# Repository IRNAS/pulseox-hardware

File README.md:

# pulseox-hardware

---

#### License

All our projects are as usefully open-source as possible.

Hardware including documentation is licensed under [CERN OHL v.1.2. license](http://www.ohwr.org/licenses/cern-ohl/v1.2)

Firmware and software originating from the project is licensed under [GNU GENERAL PUBLIC LICENSE v3](http://www.gnu.org/licenses/gpl-3.0.en.html).

Open data generated by our projects is licensed under [CC0](https://creativecommons.org/publicdomain/zero/1.0/legalcode).

All our websites and additional documentation are licensed under [Creative Commons Attribution-ShareAlike 4 .0 Unported License] (https://creativecommons.org/licenses/by-sa/4.0/legalcode).

What this means is that you can use hardware, firmware, software and documentation without paying a royalty and knowing that you'll be able to use your version forever. You are also free to make changes but if you share these changes then you have to do so on the same conditions that you enjoy.

Koruza, GoodEnoughCNC and IRNAS are all names and marks of Institut IRNAS Rače. 
You may use these names and terms only to attribute the appropriate entity as required by the Open Licences referred to above. You may not use them in any other way and in particular you may not use them to imply endorsement or authorization of any hardware that you design, make or sell.

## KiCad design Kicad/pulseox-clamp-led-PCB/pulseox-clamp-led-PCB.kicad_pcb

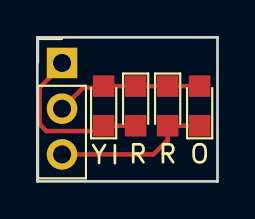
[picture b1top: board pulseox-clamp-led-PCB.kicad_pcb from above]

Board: 2 copper layers, 10.0 x 8.0 mm, 5 parts (0 on the bottom side), 3 nets.

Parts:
I: LED; LED_0805
O: LED; LED_0805
P1: Header 3; Pin_Header_Straight_1x03_Pitch2.54mm
R: LED; LED_0805
Y: LED; LED_0805

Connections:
unnamed: I.2, P1.1, Y.1
unnamed: I.1, O.2, P1.2, R.1, Y.2
unnamed: O.1, P1.3, R.2

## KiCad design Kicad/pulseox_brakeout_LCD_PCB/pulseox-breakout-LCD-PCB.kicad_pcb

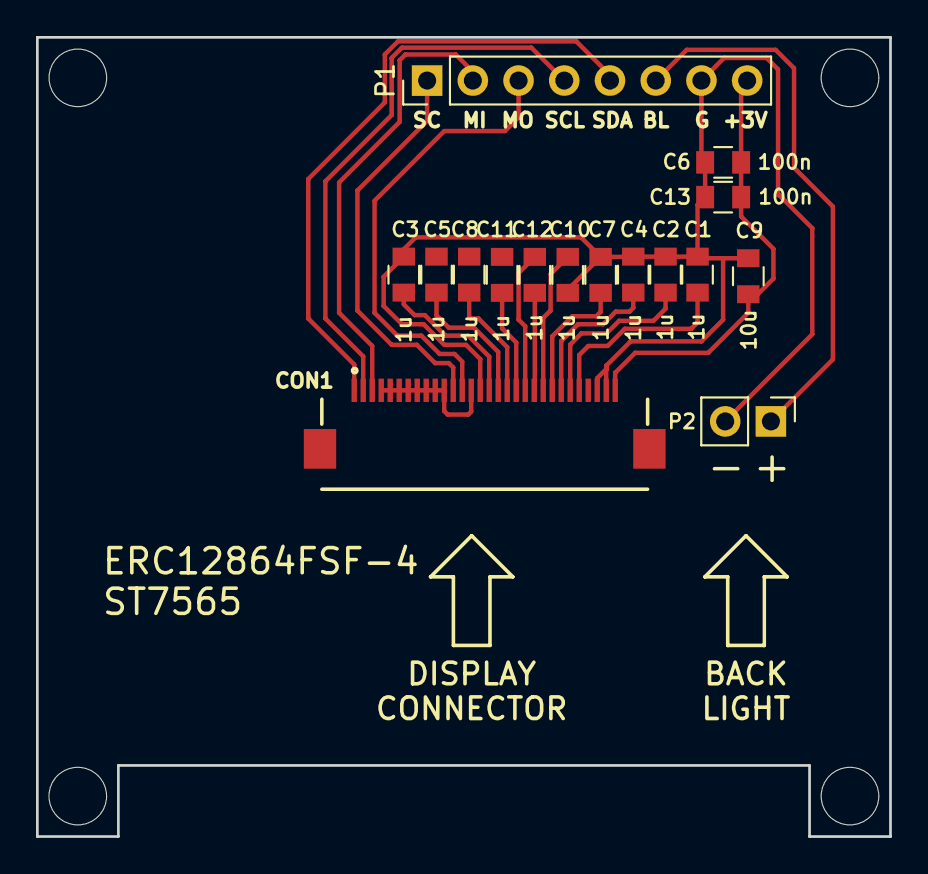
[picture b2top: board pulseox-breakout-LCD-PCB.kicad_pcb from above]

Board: 2 copper layers, 47.4 x 44.4 mm, 20 parts (0 on the bottom side), 20 nets.

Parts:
C1, C2, C3, C4, C5, C7, C8, C10, C11, C12: 1u; C_0805
C6, C13: 100n; C_0805
C9: 10u; C_0805
CON1: P3; FH12-30S-0.5SH(55)
MK1, MK2, MK3, MK4: Mounting_Hole; MountingHole_3.2mm_M3
P1: Header 8; Pin_Header_Straight_1x08_Pitch2.54mm
P2: Header 2; Pin_Header_Straight_1x02_Pitch2.54mm

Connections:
+3V3: C6.2, C9.2, C13.2, CON1.4, CON1.5, CON1.6, CON1.7, CON1.8, CON1.9, CON1.10, CON1.11, CON1.14, CON1.30, P1.8
B_LIGHT: P1.6, P2.1
GND: C1.1, C2.1, C3.1, C4.1, C6.1, C7.1, C9.1, C10.1, C13.1, CON1.15, CON1.28, CON1.29, P1.7, P2.2
unnamed: C1.2, CON1.26
unnamed: C2.2, CON1.25
unnamed: C3.2, CON1.16
unnamed: C4.2, CON1.24
unnamed: C5.2, CON1.17
unnamed: C7.2, CON1.23
unnamed: C8.2, CON1.18
unnamed: C10.2, CON1.22
unnamed: C5.1, C8.1, C11.1
unnamed: C11.2, CON1.19
unnamed: C12.1, CON1.20
unnamed: C12.2, CON1.21
PA5/SCK: CON1.12, P1.1
PA6/MISO: CON1.3, P1.2
PA7/MOSI: CON1.13, P1.3
PA9/SCL: CON1.2, P1.4
PA10/SDA: CON1.1, P1.5

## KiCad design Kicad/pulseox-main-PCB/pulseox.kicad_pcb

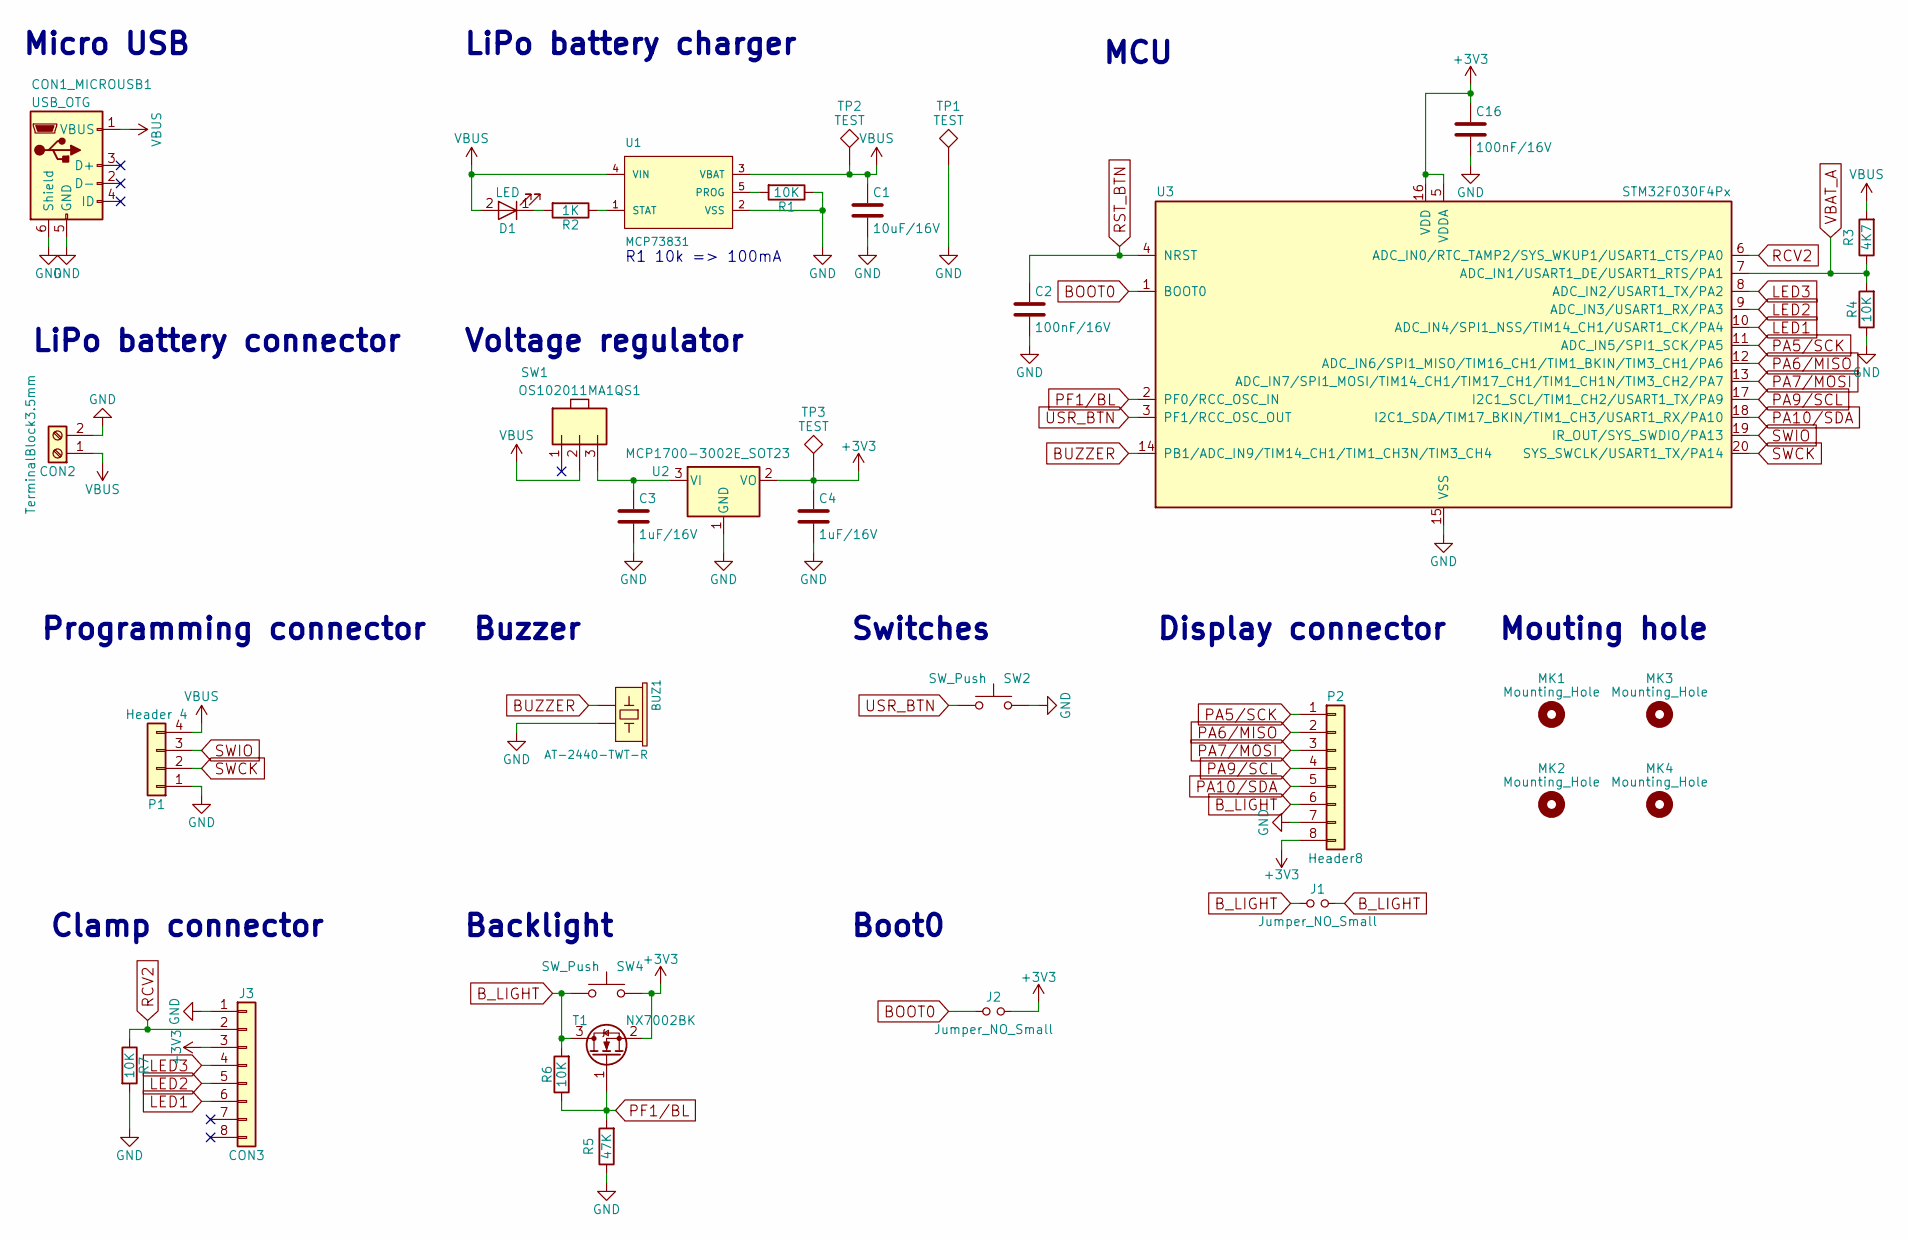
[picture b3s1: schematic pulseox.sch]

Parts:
BUZ1: AT-2440-TWT-R
C1: 10uF/16V; C_0805
C2, C16: 100nF/16V; C_0805
C3, C4: 1uF/16V; C_0805
CON1_MICROUSB1: USB_OTG; USB_Micro-B_Molex-105017-0001
CON2: TerminalBlock3.5mm; TerminalBlock_Phoenix_PT-3.5mm_2pol
D1: LED; LED_0603
J1: Jumper_NO_Small; R_0805
J2: Jumper_NO_Small; SMT-JUMPER_2_NO_SILK
J3: CON3; RJ45_8
MK1, MK2, MK3, MK4: Mounting_Hole; MountingHole_3.2mm_M3_ISO7380
P1: Header 4; Pin_Header_Straight_1x04_Pitch2.54mm
P2: Header8; Pin_Header_Straight_1x08_Pitch2.54mm
R1: 10K; R_0603
R2: 1K; R_0603
R3: 4K7; R_0805
R4, R6, R7: 10K; R_0805
R5: 47K; R_0805
SW1: OS102011MA1QS1
SW2, SW4: SW_Push; SWITCH TACTILE SPST-NO 0.05A 12V
T1: NX7002BK; SOT65P210X110-3N
TP1, TP2, TP3: TEST; Measurement_Point_Round-SMD-Pad_Small
U1: MCP73831; SOT23-5
U2: MCP1700-3002E_SOT23; SOT-23
U3: STM32F030F4Px; TSSOP-20_4.4x6.5mm_Pitch0.65mm

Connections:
+3V3: C4.1, C16.1, J2.2, J3.3, P2.8, SW4.2, T1.2 (S), TP3.1, U2.2 (VO), U3.5 (VDDA), U3.16 (VDD)
BOOT0: J2.1, U3.1 (BOOT0)
BUZZER: BUZ1.+ (1), U3.14 (PB1/ADC_IN9/TIM14_CH1/TIM1_CH3N/TIM3_CH4)
B_LIGHT: J1.1, J1.2, P2.6, R6.2, SW4.1, T1.3 (D)
GND: BUZ1.- (2), C1.2, C2.2, C3.2, C4.2, C16.2, CON1_MICROUSB1.5 (GND), CON1_MICROUSB1.6 (Shield), CON2.2, J3.1, P1.1, P2.7, R1.1, R4.1, R5.1, R7.2, SW2.2, TP1.1, U1.2 (VSS), U2.1 (GND), U3.15 (VSS)
LED1: J3.6, U3.10 (ADC_IN4/SPI1_NSS/TIM14_CH1/USART1_CK/PA4)
LED2: J3.5, U3.9 (ADC_IN3/USART1_RX/PA3)
LED3: J3.4, U3.8 (ADC_IN2/USART1_TX/PA2)
unnamed: C3.1, SW1.3, U2.3 (VI)
unnamed: D1.1 (K), R2.2
unnamed: R1.2, U1.5 (PROG)
unnamed: R2.1, U1.1 (STAT)
PA5/SCK: P2.1, U3.11 (ADC_IN5/SPI1_SCK/PA5)
PA6/MISO: P2.2, U3.12 (ADC_IN6/SPI1_MISO/TIM16_CH1/TIM1_BKIN/T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)
PA7/MOSI: P2.3, U3.13 (ADC_IN7/SPI1_MOSI/TIM14_CH1/TIM17_CH1/T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)
PA9/SCL: P2.4, U3.17 (I2C1_SCL/TIM1_CH2/USART1_TX/PA9)
PA10/SDA: P2.5, U3.18 (I2C1_SDA/TIM17_BKIN/TIM1_CH3/USART1_RX/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)
PF1/BL: R5.2, R6.1, T1.1 (G), U3.2 (PF0/RCC_OSC_IN)
RCV2: J3.2, R7.1, U3.6 (ADC_IN0/RTC_TAMP2/SYS_WKUP1/USART1_CTS/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)
RST_BTN: C2.1, U3.4 (NRST)
SWCK: P1.2, U3.20 (SYS_SWCLK/USART1_TX/PA14)
SWIO: P1.3, U3.19 (IR_OUT/SYS_SWDIO/PA13)
USR_BTN: SW2.1, U3.3 (PF1/RCC_OSC_OUT)
VBAT_A: R3.1, R4.2, U3.7 (ADC_IN1/USART1_DE/USART1_RTS/PA1)
VBUS: C1.1, CON1_MICROUSB1.1 (VBUS), CON2.1, D1.2 (A), P1.4, R3.2, SW1.2, TP2.1, U1.3 (VBAT), U1.4 (VIN)

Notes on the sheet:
R1 10k => 100mA
Micro USB
LiPo battery charger
LiPo battery connector
Voltage regulator
Programming connector
Buzzer
Clamp connector
Backlight
Switches
Boot0
MCU
Display connector
Mouting hole

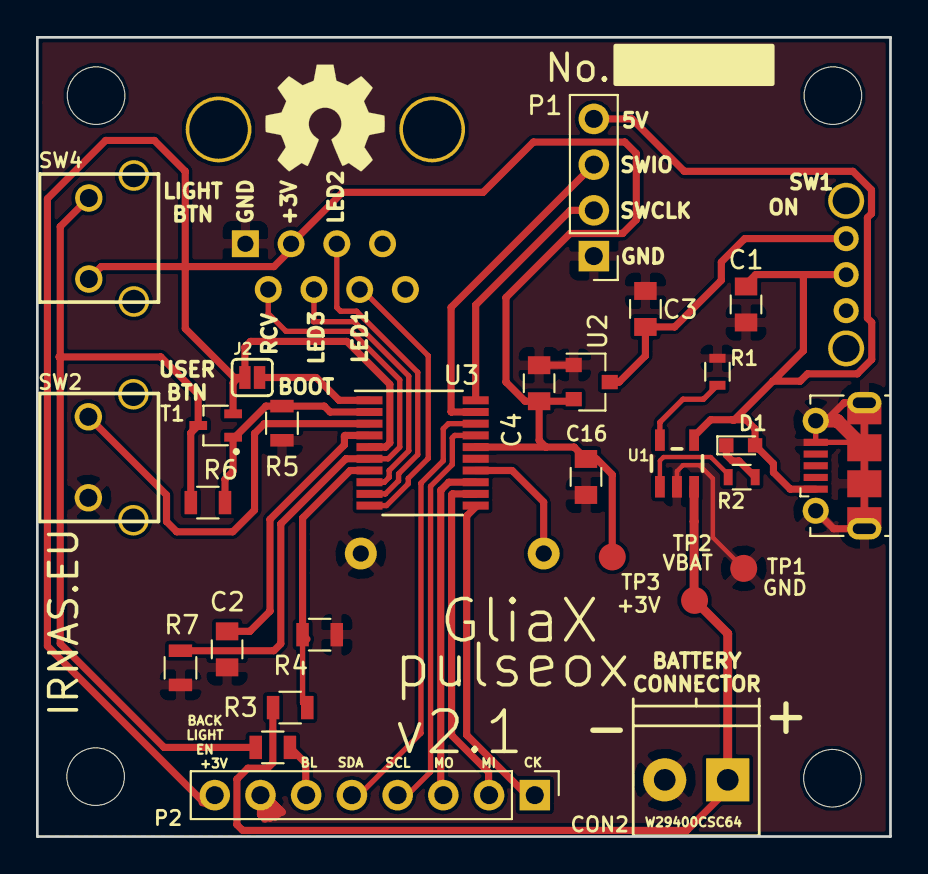
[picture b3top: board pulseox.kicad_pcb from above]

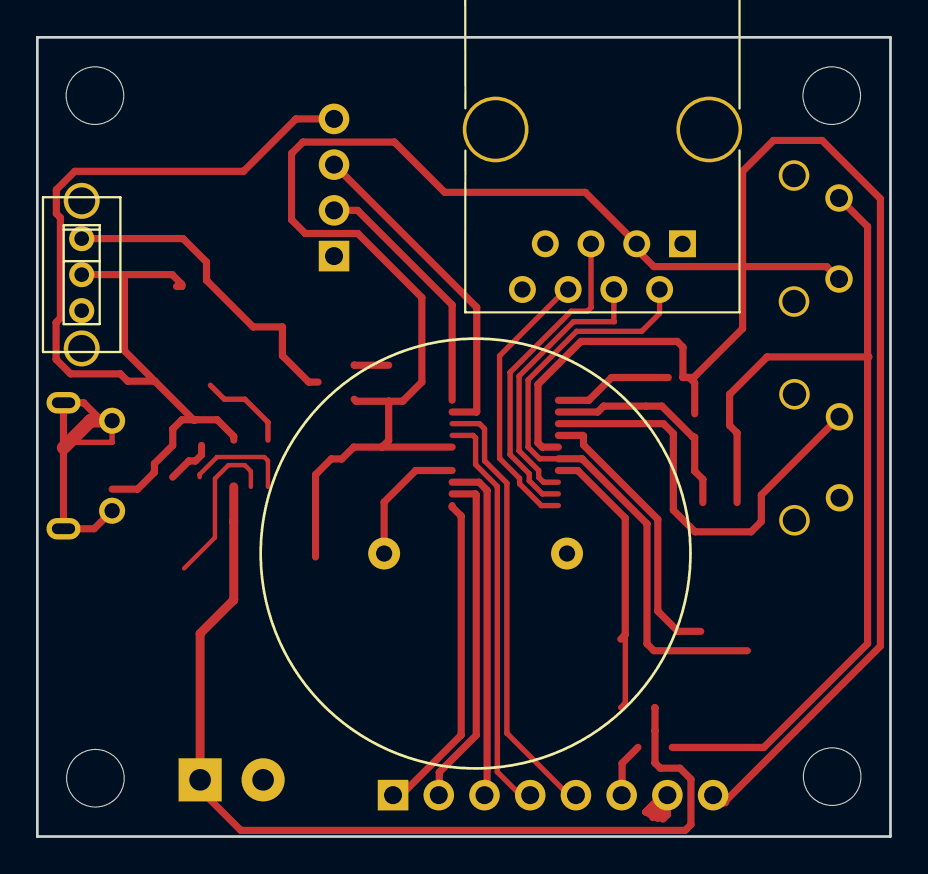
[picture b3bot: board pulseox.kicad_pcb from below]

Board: 2 copper layers, 47.4 x 44.4 mm, 35 parts (3 on the bottom side), 25 nets.

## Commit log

2017-04-18 Added Schematics
2017-04-19 Updated schematic
2017-04-19 updated pdf
2017-04-19 saved project
2017-07-19 git ignore main pcb
2017-07-19 new project
2017-07-19 main pcb outline
2017-07-20 sch done, need to be reviewed
2017-08-07 sch and pcb shape update
2017-08-08 new version v2.0 done
2017-08-08 documentation update
2017-08-08 clamp pcb project
2017-08-09 clamp pcb update
2017-08-10 pcb update v2.0 gerbers done
2017-10-13 Rename soldering.md to 01_soldering.md
2017-10-16 Rename 01 firmware flashing instructions.md to 01_firmware_flashing_instructions.md
2017-10-16 Create 03_debugging
2017-10-23 Rename 03_debugging to 03_debugging.md
2018-01-04 Rename Housing and Finger Clip/build_files/README.md to Housing and Finger Clip/housing/README.md
2018-01-04 Rename Housing and Finger Clip/build_files/case_bottom.STEP to Housing and Finger Clip/housing/case_bottom.STEP
2018-01-04 Create dummy
2018-01-04 Rename Housing and Finger Clip/housing/case_bottom.STEP to Housing and Finger Clip/housing/build_files/case_bottom.STEP
2018-01-04 Rename Housing and Finger Clip/build_files_V2/README.md to Housing and Finger Clip/finger_clip/README.md
2018-02-20 new version of pulseox
2018-07-16 v2.1 finished design
2018-07-17 update docs
2018-07-18 Added Kicad files
2018-07-18 Added output PDF files from Kicad project
